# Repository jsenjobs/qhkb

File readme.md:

# qh-ws42-v2

    42键无线分体，主控nrf52840

# qh-s42-v5

    42键有线小红点分体，主控apm32f103cbt6，兼容3x5配列，还没测过。
    固件部分源码在 vial-qmk 下。

# --

    如果有自己设计好的键盘外壳，联系我，分享一下。

    交流咨询可以咸鱼搜qhkb。
    QQ：1922279340

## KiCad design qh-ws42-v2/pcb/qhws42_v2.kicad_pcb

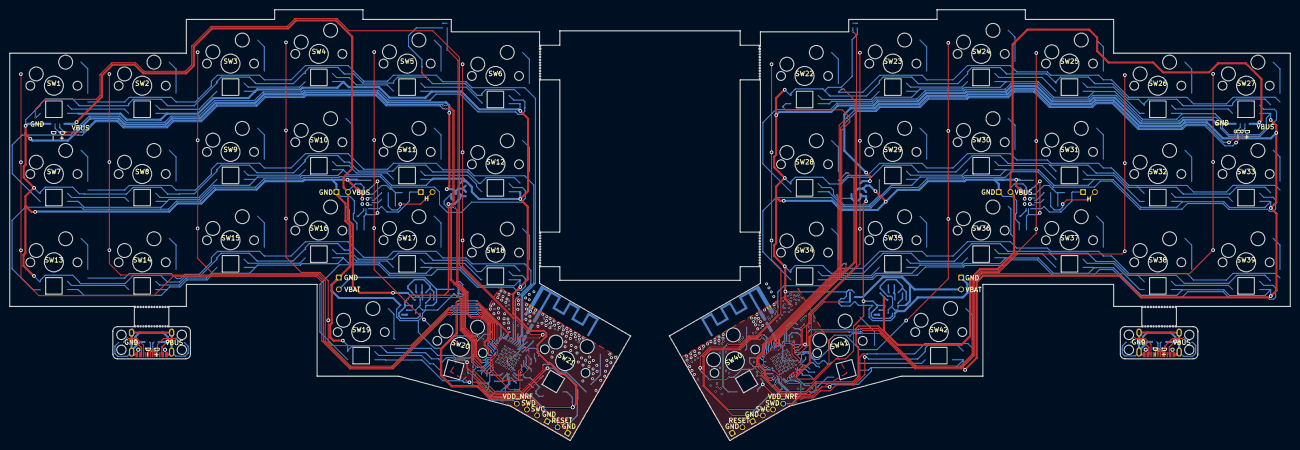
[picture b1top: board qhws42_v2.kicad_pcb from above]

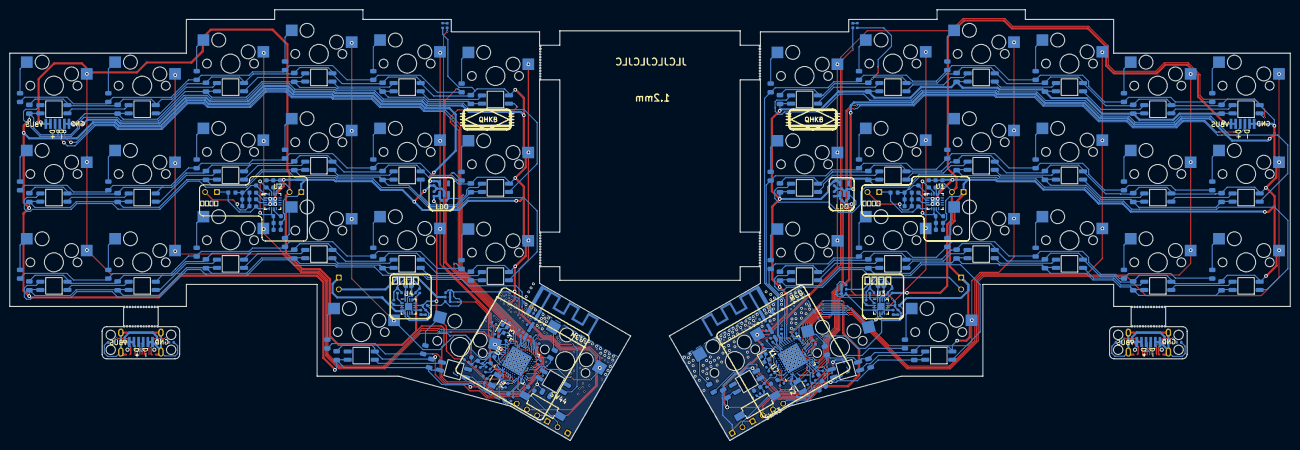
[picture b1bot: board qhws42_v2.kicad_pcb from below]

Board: 2 copper layers, 276.2 x 92.9 mm, 316 parts (272 on the bottom side), 204 nets.

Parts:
AE1: Antenna_Shield; ANT_LEFT
AE2: Antenna_Shield; ANT_RIGHT
C1, C2, C3, C4, C5, C6, C7, C8, C9, C10, C11, C12, C13, C14, C15, C16, C17, C18, C19, C20, C21, C22, C23, C24, C25, C26, C27, C28, C29, C30, C31, C32, C33, C34, C35, C36, C37, C38, C39, C40, C41, C42: C; C_0805_2012Metric
C43, C50, C54, C63: 100nF; C_0603_1608Metric
C44, C46, C47, C55, C58, C59: 47nF; C_0603_1608Metric
C45, C56: 33nF; C_0603_1608Metric
C48, C57: 2.2nF; C_0603_1608Metric
C49, C51, C52, C60, C61, C62: 10uF; C_0603_1608Metric
C53, C64, C94, C116: 1uF; C_0603_1608Metric
C65, C68, C85, C107: 1uF; C_0402_1005Metric
C66, C67, C69, C70, C72, C75, C77, C91, C92, C99, C113, C114: 4.7uF; C_0402_1005Metric
C71, C74: 10uF; C_0402_1005Metric
C73, C76, C78, C80, C81, C87, C100, C102, C103, C109: 100nF; C_0402_1005Metric
C79, C88, C96, C101, C110, C118: N.C.; C_0402_1005Metric
C82, C86, C104, C108: 1pF; C_0402_1005Metric
C83, C84, C97, C98, C105, C106, C119, C120: 12pF; C_0402_1005Metric
C89, C111: 100pF; C_0402_1005Metric
C90, C112: 820pF; C_0402_1005Metric
C93, C115: 4.7uF; C_0603_1608Metric
C95, C117: 47nF; C_0402_1005Metric
D1, D2, D3, D4, D5, D6, D7, D8, D9, D10, D11, D12, D13, D14, D15, D16, D17, D18, D19, D20, D21, D22, D23, D24, D25, D26, D27, D28, D29, D30, D31, D32, D33, D34, D35, D36, D37, D38, D39, D40, D41, D42: D; D_0805_2012Metric
D43, D44: RED; LED_0402_1005Metric
D45, D46: BLUE; LED_0402_1005Metric
FFC1, FFC2, FFC3, FFC4: fpc_1mm_6pin; fpc_1mm_6pin_thin
J1, J3: 15.8uH; connector_2pin
J2, J4: VOUT; connector_2pin
J5, J7: Conn_01x04; connector_swd
J6, J8, J9, J10: Conn_01x02; connector_2pin
JP1, JP2: Boost; SolderJumper-2_P1.3mm_Open_RoundedPad1.0x1.5mm
L1, L5: 3.9nH; L_0402_1005Metric
L2, L6: 15nH; L_0402_1005Metric
L3, L4, L7, L8: 10uH; L_0603_1608Metric
LED1, LED2, LED3, LED4, LED5, LED6, LED7, LED8, LED9, LED10, LED11, LED12, LED13, LED14, LED15, LED16, LED17, LED18, LED19, LED20, LED21, LED22, LED23, LED24, LED25, LED26, LED27, LED28, LED29, LED30, LED31, LED32, LED33, LED34, LED35, LED36, LED37, LED38, LED39, LED40, LED41, LED42: rgb_4pin; rgb_3528
R1, R2: 220R; R_0603_1608Metric
R3, R7: 2k; R_0402_1005Metric
R4, R5, R6, R8, R9, R10: 10k; R_0402_1005Metric
R11, R14: 10M; R_0402_1005Metric
R12, R15: 820k; R_0402_1005Metric
R13, R16: 2M; R_0402_1005Metric
R17, R19: 0r; R_0402_1005Metric
R18, R20: 1k; R_0402_1005Metric
R21, R22, R23, R24: 5.1k; R_0402_1005Metric
SW1, SW2, SW3, SW4, SW5, SW6, SW7, SW8, SW9, SW10, SW11, SW12, SW13, SW14, SW15, SW16, SW17, SW18, SW19, SW20, SW21, SW22, SW23, SW24, SW25, SW26, SW27, SW28, SW29, SW30, SW31, SW32, SW33, SW34, SW35, SW36, SW37, SW38, SW39, SW40, SW41, SW42: sw_qhkb; switch_hotswap_1u
SW43, SW44: Reed_GPS-11A-SMD; Reed_SW-RI-80SMD-1015-G2
U1, U2: KICAD_NU1680; KICAD_QFN-16_L3.0-W3.0-P0.50-TL-EP1.9
U3, U4: BQ24075RGT; VQFN-16-1EP_3x3mm_P0.5mm_EP1.6x1.6mm
U5, U6: XC6220B331MR; SOT-23-5
U7, U8: nRF52840; Nordic_AQFN-73-1EP_7x7mm_P0.5mm
USB1, USB2: TYPE-C_16PIN_2MD(073); USB-C-SMD_TYPE-C-6PIN-2MD-073
Y1, Y3: 32MHz; Crystal_SMD_2016-4Pin_2.0x1.6mm
Y2, Y4: 32.768kHz; Crystal_SMD_3215-2Pin_3.2x1.5mm

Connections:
/D+_TC_l: FFC3.4, USB1.6 (DP1), USB1.8 (DP2)
/D+_TC_r: FFC4.4, USB2.6 (DP1), USB2.8 (DP2)
/D-_TC_l: FFC3.3, USB1.5 (DN2), USB1.7 (DN1)
/D-_TC_r: FFC4.3, USB2.5 (DN2), USB2.7 (DN1)
/GND_TC_l: FFC3.1, FFC3.2, R21.2, R22.2, USB1.1 (GND), USB1.12 (GND), USB1.13 (SHELL), USB1.14 (SHELL)
/GND_TC_r: FFC4.1, FFC4.2, R23.2, R24.2, USB2.1 (GND), USB2.12 (GND), USB2.13 (SHELL), USB2.14 (SHELL)
/VBUS_TC_l: FFC3.5, FFC3.6, USB1.2 (VBUS), USB1.11 (VBUS)
/VBUS_TC_r: FFC4.5, FFC4.6, USB2.2 (VBUS), USB2.11 (VBUS)
/VRECT_l: C49.2, C50.2, C51.2, R1.1, U1.6 (VRECT), U1.15 (VRECT)
/VRECT_r: C61.2, C62.2, C63.2, R2.1, U2.6 (VRECT), U2.15 (VRECT)
ANTENNA_l: AE1.1 (A), C79.2, R17.1
ANTENNA_r: AE2.1 (A), C101.2, R19.1
BATTERY_LEVEL_PIN_l: C73.2, R12.1, R13.2, U7.J1 (AIN2/P0.04)
BATTERY_LEVEL_PIN_r: C76.2, R15.1, R16.2, U8.J1 (AIN2/P0.04)
BLED_l: D45.2 (A), U7.AD10 (P0.15)
BLED_r: D46.2 (A), U8.A16 (P1.13)
COL0_l: SW1.1, SW7.1, SW13.1, U7.AD12 (P0.17)
COL0_r: SW22.1, SW28.1, SW34.1, SW40.1, U8.AD12 (P0.17)
COL1_l: SW2.1, SW8.1, SW14.1, U7.AD16 (P0.20)
COL1_r: SW23.1, SW29.1, SW35.1, SW41.1, U8.A20 (P1.10)
COL2_l: SW3.1, SW9.1, SW15.1, U7.AD18 (P0.22)
COL2_r: SW24.1, SW30.1, SW36.1, SW42.1, U8.A14 (P1.15)
COL3_l: SW4.1, SW10.1, SW16.1, SW19.1, U7.AD20 (P0.24)
COL3_r: SW25.1, SW31.1, SW37.1, U8.A12 (AIN0/P0.02)
COL4_l: SW5.1, SW11.1, SW17.1, SW20.1, U7.AD22 (TRACEDATA0/P1.00)
COL4_r: SW26.1, SW32.1, SW38.1, U8.L1 (P0.06)
COL5_l: SW6.1, SW12.1, SW18.1, SW21.1, U7.W24 (P1.02)
COL5_r: SW27.1, SW33.1, SW39.1, U8.N1 (P0.08)
D+_l: FFC1.3, U7.AD6 (D+)
D+_r: FFC2.3, U8.AD6 (D+)
D-_l: FFC1.4, U7.AD4 (D-)
D-_r: FFC2.4, U8.AD4 (D-)
EXT_VCC_l: C1.2, C2.2, C3.2, C4.2, C5.2, C6.2, C7.2, C8.2, C9.2, C10.2, C11.2, C12.2, C13.2, C14.2, C15.2, C16.2, C17.2, C18.2, C19.2, C20.2, C21.2, C72.2, LED1.1 (VDD), LED2.1 (VDD), LED3.1 (VDD), LED4.1 (VDD), LED5.1 (VDD), LED6.1 (VDD), LED7.1 (VDD), LED8.1 (VDD), LED9.1 (VDD), LED10.1 (VDD), LED11.1 (VDD), LED12.1 (VDD), LED13.1 (VDD), LED14.1 (VDD), LED15.1 (VDD), LED16.1 (VDD), LED17.1 (VDD), LED18.1 (VDD), LED19.1 (VDD), LED20.1 (VDD), LED21.1 (VDD), U5.5 (VOUT)
EXT_VCC_r: C22.2, C23.2, C24.2, C25.2, C26.2, C27.2, C28.2, C29.2, C30.2, C31.2, C32.2, C33.2, C34.2, C35.2, C36.2, C37.2, C38.2, C39.2, C40.2, C41.2, C42.2, C75.2, LED22.1 (VDD), LED23.1 (VDD), LED24.1 (VDD), LED25.1 (VDD), LED26.1 (VDD), LED27.1 (VDD), LED28.1 (VDD), LED29.1 (VDD), LED30.1 (VDD), LED31.1 (VDD), LED32.1 (VDD), LED33.1 (VDD), LED34.1 (VDD), LED35.1 (VDD), LED36.1 (VDD), LED37.1 (VDD), LED38.1 (VDD), LED39.1 (VDD), LED40.1 (VDD), LED41.1 (VDD), LED42.1 (VDD), U6.5 (VOUT)
GND_l: AE1.2 (Shield), C1.1, C2.1, C3.1, C4.1, C5.1, C6.1, C7.1, C8.1, C9.1, C10.1, C11.1, C12.1, C13.1, C14.1, C15.1, C16.1, C17.1, C18.1, C19.1, C20.1, C21.1, C49.1, C50.1, C51.1, C52.2, C53.1, C65.1, C66.1, C67.1, C71.1, C72.1, C73.1, C77.1, C78.1, C79.1, C80.1, C81.1, C82.1, C83.1, C84.2, C85.1, C86.1, C87.1, C88.1, C89.1, C90.2, C91.1, C92.2, C93.2, C94.2, C95.2, C96.2, C97.2, C98.2, FFC1.5, FFC1.6, J2.1, J5.1, J6.1, J9.1, LED1.3 (VSS), LED2.3 (VSS), LED3.3 (VSS), LED4.3 (VSS), LED5.3 (VSS), LED6.3 (VSS), LED7.3 (VSS), LED8.3 (VSS), LED9.3 (VSS), LED10.3 (VSS), LED11.3 (VSS), LED12.3 (VSS), LED13.3 (VSS), LED14.3 (VSS), LED15.3 (VSS), LED16.3 (VSS), LED17.3 (VSS), LED18.3 (VSS), LED19.3 (VSS), LED20.3 (VSS), LED21.3 (VSS), R3.2, R4.1, R5.2, R13.1, R18.2, SW43.2, U1.1 (GND), U1.4 (GND), U1.17 (EP), U3.4 (~CE), U3.5 (EN2), U3.8 (VSS), U3.15 (SYSOFF), U3.17 (VSS), U5.2 (GND), U7.B7 (VSS), U7.EP (VSS), U7.F23 (VSS_PA), Y1.2, Y1.4
GND_r: AE2.2 (Shield), C22.1, C23.1, C24.1, C25.1, C26.1, C27.1, C28.1, C29.1, C30.1, C31.1, C32.1, C33.1, C34.1, C35.1, C36.1, C37.1, C38.1, C39.1, C40.1, C41.1, C42.1, C60.2, C61.1, C62.1, C63.1, C64.1, C68.1, C69.1, C70.1, C74.1, C75.1, C76.1, C99.1, C100.1, C101.1, C102.1, C103.1, C104.1, C105.1, C106.2, C107.1, C108.1, C109.1, C110.1, C111.1, C112.2, C113.1, C114.2, C115.2, C116.2, C117.2, C118.2, C119.2, C120.2, FFC2.5, FFC2.6, J4.1, J7.1, J8.1, J10.1, LED22.3 (VSS), LED23.3 (VSS), LED24.3 (VSS), LED25.3 (VSS), LED26.3 (VSS), LED27.3 (VSS), LED28.3 (VSS), LED29.3 (VSS), LED30.3 (VSS), LED31.3 (VSS), LED32.3 (VSS), LED33.3 (VSS), LED34.3 (VSS), LED35.3 (VSS), LED36.3 (VSS), LED37.3 (VSS), LED38.3 (VSS), LED39.3 (VSS), LED40.3 (VSS), LED41.3 (VSS), LED42.3 (VSS), R7.2, R8.1, R9.2, R16.1, R20.2, SW44.2, U2.1 (GND), U2.4 (GND), U2.17 (EP), U4.4 (~CE), U4.5 (EN2), U4.8 (VSS), U4.15 (SYSOFF), U4.17 (VSS), U6.2 (GND), U8.B7 (VSS), U8.EP (VSS), U8.F23 (VSS_PA), Y3.2, Y3.4
unnamed: C82.2, L1.1, R17.2
unnamed: C104.2, L5.1, R19.2
unnamed: D1.2 (A), SW1.2
unnamed: D2.2 (A), SW2.2
unnamed: D3.2 (A), SW3.2
unnamed: D4.2 (A), SW4.2
unnamed: D5.2 (A), SW5.2
unnamed: D6.2 (A), SW6.2
unnamed: D7.2 (A), SW7.2
unnamed: D8.2 (A), SW8.2
unnamed: D9.2 (A), SW9.2
unnamed: D10.2 (A), SW10.2
unnamed: D11.2 (A), SW11.2
unnamed: D12.2 (A), SW12.2
unnamed: D13.2 (A), SW13.2
unnamed: D14.2 (A), SW14.2
unnamed: D15.2 (A), SW15.2
unnamed: D16.2 (A), SW16.2
unnamed: D17.2 (A), SW17.2
unnamed: D18.2 (A), SW18.2
unnamed: D19.2 (A), SW19.2
unnamed: D20.2 (A), SW20.2
unnamed: D21.2 (A), SW21.2
unnamed: D22.2 (A), SW22.2
unnamed: D23.2 (A), SW23.2
unnamed: D24.2 (A), SW24.2
unnamed: D25.2 (A), SW25.2
unnamed: D26.2 (A), SW26.2
unnamed: D27.2 (A), SW27.2
unnamed: D28.2 (A), SW28.2
unnamed: D29.2 (A), SW29.2
unnamed: D30.2 (A), SW30.2
unnamed: D31.2 (A), SW31.2
unnamed: D32.2 (A), SW32.2
unnamed: D33.2 (A), SW33.2
unnamed: D34.2 (A), SW34.2
unnamed: D35.2 (A), SW35.2
unnamed: D36.2 (A), SW36.2
unnamed: D37.2 (A), SW37.2
unnamed: D38.2 (A), SW38.2
unnamed: D39.2 (A), SW39.2
unnamed: D40.2 (A), SW40.2
unnamed: D41.2 (A), SW41.2
unnamed: D42.2 (A), SW42.2
unnamed: D43.2 (A), R6.1
unnamed: D43.1 (K), U3.9 (~CHG)
unnamed: D44.2 (A), R10.1
unnamed: D44.1 (K), U4.9 (~CHG)
unnamed: D45.1 (K), R18.1
unnamed: D46.1 (K), R20.1
unnamed: C47.1, C48.1, J1.1, U1.5 (AC2)
unnamed: C43.1, C44.1, C45.1, J1.2
unnamed: C57.1, C59.1, J3.1, U2.5 (AC2)
unnamed: C54.1, C55.1, C56.1, J3.2
unnamed: JP1.2, R3.1
unnamed: JP2.2, R7.1
unnamed: L2.2, L3.1
unnamed: L6.2, L7.1
unnamed: LED1.2 (DOUT), LED2.4 (DIN)
unnamed: LED2.2 (DOUT), LED3.4 (DIN)
unnamed: LED3.2 (DOUT), LED4.4 (DIN)
unnamed: LED4.2 (DOUT), LED5.4 (DIN)
unnamed: LED5.2 (DOUT), LED6.4 (DIN)
unnamed: LED6.2 (DOUT), LED7.4 (DIN)
unnamed: LED7.2 (DOUT), LED8.4 (DIN)
unnamed: LED8.2 (DOUT), LED9.4 (DIN)
unnamed: LED9.2 (DOUT), LED10.4 (DIN)
unnamed: LED10.2 (DOUT), LED11.4 (DIN)
unnamed: LED11.2 (DOUT), LED12.4 (DIN)
unnamed: LED12.2 (DOUT), LED13.4 (DIN)
unnamed: LED13.2 (DOUT), LED14.4 (DIN)
unnamed: LED14.2 (DOUT), LED15.4 (DIN)
unnamed: LED15.2 (DOUT), LED16.4 (DIN)
unnamed: LED16.2 (DOUT), LED17.4 (DIN)
unnamed: LED17.2 (DOUT), LED18.4 (DIN)
unnamed: LED18.2 (DOUT), LED19.4 (DIN)
unnamed: LED19.2 (DOUT), LED20.4 (DIN)
unnamed: LED20.2 (DOUT), LED21.4 (DIN)
unnamed: LED22.2 (DOUT), LED23.4 (DIN)
unnamed: LED23.2 (DOUT), LED24.4 (DIN)
unnamed: LED24.2 (DOUT), LED25.4 (DIN)
unnamed: LED25.2 (DOUT), LED26.4 (DIN)
unnamed: LED26.2 (DOUT), LED27.4 (DIN)
unnamed: LED27.2 (DOUT), LED28.4 (DIN)
unnamed: LED28.2 (DOUT), LED29.4 (DIN)
unnamed: LED29.2 (DOUT), LED30.4 (DIN)
unnamed: LED30.2 (DOUT), LED31.4 (DIN)
unnamed: LED31.2 (DOUT), LED32.4 (DIN)
unnamed: LED32.2 (DOUT), LED33.4 (DIN)
unnamed: LED33.2 (DOUT), LED34.4 (DIN)
unnamed: LED34.2 (DOUT), LED35.4 (DIN)
unnamed: LED35.2 (DOUT), LED36.4 (DIN)
unnamed: LED36.2 (DOUT), LED37.4 (DIN)
unnamed: LED37.2 (DOUT), LED38.4 (DIN)
unnamed: LED38.2 (DOUT), LED39.4 (DIN)
unnamed: LED39.2 (DOUT), LED40.4 (DIN)
unnamed: LED40.2 (DOUT), LED41.4 (DIN)
unnamed: LED41.2 (DOUT), LED42.4 (DIN)
unnamed: C43.2, C44.2, C45.2, C46.2, C48.2, U1.16 (AC1)
unnamed: C46.1, U1.2 (COMM1)
unnamed: C47.2, U1.3 (COMM2)
unnamed: R1.2, U1.7 (SINK)
unnamed: C53.2, U1.13 (V5V)
unnamed: C54.2, C55.2, C56.2, C57.2, C58.2, U2.16 (AC1)
unnamed: C58.1, U2.2 (COMM1)
unnamed: C59.2, U2.3 (COMM2)
unnamed: R2.2, U2.7 (SINK)
unnamed: C64.2, U2.13 (V5V)
unnamed: JP1.1, R4.2, U3.16 (ISET)
unnamed: R5.1, U3.1 (TS)
unnamed: JP2.1, R8.2, U4.16 (ISET)
unnamed: R9.1, U4.1 (TS)
unnamed: C86.2, L1.2, U7.H23 (ANT)
unnamed: L3.2, U7.B3 (DCC)
unnamed: L4.1, U7.AB2 (DCCH)
unnamed: C87.2, U7.C1 (DEC1)
unnamed: C88.2, U7.A18 (DEC2)
unnamed: C89.2, U7.D23 (DEC3)
unnamed: C94.1, C95.1, C96.1, L2.1, U7.B5 (DEC4), U7.E24 (DEC6)
unnamed: C90.1, U7.N24 (DEC5)
unnamed: C91.2, U7.AC5 (DECUSB)
unnamed: C83.2, U7.B24 (XC1), Y1.1
unnamed: C84.1, U7.A23 (XC2), Y1.3
unnamed: C97.1, U7.D2 (XL1/P0.00), Y2.2
unnamed: C98.1, U7.F2 (XL2/P0.01), Y2.1
unnamed: C108.2, L5.2, U8.H23 (ANT)
unnamed: L7.2, U8.B3 (DCC)
unnamed: L8.1, U8.AB2 (DCCH)
unnamed: C109.2, U8.C1 (DEC1)
unnamed: C110.2, U8.A18 (DEC2)
unnamed: C111.2, U8.D23 (DEC3)
unnamed: C116.1, C117.1, C118.1, L6.1, U8.B5 (DEC4), U8.E24 (DEC6)
unnamed: C112.1, U8.N24 (DEC5)
unnamed: C113.2, U8.AC5 (DECUSB)
unnamed: C105.2, U8.B24 (XC1), Y3.1
unnamed: C106.1, U8.A23 (XC2), Y3.3
unnamed: C119.1, U8.D2 (XL1/P0.00), Y4.2
unnamed: C120.1, U8.F2 (XL2/P0.01), Y4.1
unnamed: R22.1, USB1.4 (CC1)
unnamed: R21.1, USB1.10 (CC2)
unnamed: R24.1, USB2.4 (CC1)
unnamed: R23.1, USB2.10 (CC2)
POWER_PIN_l: R11.2, U5.3 (CE), U7.AD8 (P0.13)
POWER_PIN_r: R14.2, U6.3 (CE), U8.AD8 (P0.13)
RESET_l: J6.2, SW43.1, U7.AC9 (P0.14), U7.AC11 (P0.16), U7.AC13 (P0.18/~RESET)
RESET_r: J8.2, SW44.1, U8.AC9 (P0.14), U8.AC11 (P0.16), U8.AC13 (P0.18/~RESET)
RGB_l: LED1.4 (DIN), U7.U24 (P1.04)
RGB_r: LED22.4 (DIN), U8.W24 (P1.02)
ROW0_l: D1.1 (K), D2.1 (K), D3.1 (K), D4.1 (K), D5.1 (K), D6.1 (K), U7.J24 (NFC2/P0.10)
ROW0_r: D22.1 (K), D23.1 (K), D24.1 (K), D25.1 (K), D26.1 (K), D27.1 (K), U8.U24 (P1.04)
ROW1_l: D7.1 (K), D8.1 (K), D9.1 (K), D10.1 (K), D11.1 (K), D12.1 (K), U7.L24 (NFC1/P0.09)
ROW1_r: D28.1 (K), D29.1 (K), D30.1 (K), D31.1 (K), D32.1 (K), D33.1 (K), U8.L24 (NFC1/P0.09)
ROW2_l: D13.1 (K), D14.1 (K), D15.1 (K), D16.1 (K), D17.1 (K), D18.1 (K), U7.R24 (P1.06)
ROW2_r: D34.1 (K), D35.1 (K), D36.1 (K), D37.1 (K), D38.1 (K), D39.1 (K), U8.J24 (NFC2/P0.10)
ROW3_l: D19.1 (K), D20.1 (K), D21.1 (K), U7.A14 (P1.15)
ROW3_r: D40.1 (K), D41.1 (K), D42.1 (K), U8.AD20 (P0.24)
SWC_l: J5.2, U7.AA24 (SWDCLK)
SWC_r: J7.2, U8.AA24 (SWDCLK)
SWD_l: J5.3, U7.AC24 (SWDIO)
SWD_r: J7.3, U8.AC24 (SWDIO)
VBAT_l: C67.2, J9.2, R12.2, U3.2 (BAT), U3.3 (BAT)
VBAT_r: C70.2, J10.2, R15.2, U4.2 (BAT), U4.3 (BAT)
VBUS_l: C52.1, C65.2, C93.1, FFC1.1, FFC1.2, J2.2, U1.14 (VOUT), U3.13 (IN), U7.AD2 (VBUS)
VBUS_r: C60.1, C68.2, C115.1, FFC2.1, FFC2.2, J4.2, U2.14 (VOUT), U4.13 (IN), U8.AD2 (VBUS)
VDDH_l: C66.2, C71.2, C92.1, R6.2, R11.1, U3.6 (EN1), U3.10 (OUT), U3.11 (OUT), U5.1 (VIN), U7.Y2 (VDDH)
VDDH_r: C69.2, C74.2, C114.1, R10.2, R14.1, U4.6 (EN1), U4.10 (OUT), U4.11 (OUT), U6.1 (VIN), U8.Y2 (VDDH)
VDD_NRF_l: C77.2, C78.2, C80.2, C81.2, C85.2, J5.4, L4.2, U7.A22 (VDD), U7.AD14 (VDD), U7.AD23 (VDD), U7.B1 (VDD), U7.W1 (VDD)
VDD_NRF_r: C99.2, C100.2, C102.2, C103.2, C107.2, J7.4, L8.2, U8.A22 (VDD), U8.AD14 (VDD), U8.AD23 (VDD), U8.B1 (VDD), U8.W1 (VDD)

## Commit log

2023-10-21 qhws42v2
2024-01-06 Create LICENSE
2024-01-06 add qh-s42-v5
2024-01-06 add qh-s42-v5 pics
2024-01-06 add qh-ws42-v2 pics
2024-01-06 add bootloader
